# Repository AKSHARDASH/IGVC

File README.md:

# Team Anvrit - IGVC AutoNav Participation

Welcome to the repository for Team Anvrit's contribution to the IGVC AutoNav competition, hosted by Oakland University. This repository contains the schematic and board files for the custom PCB used in our vehicle.

## Overview

Our PCB design incorporates several unique features essential for tackling the problem statements of the IGVC AutoNav. The key functionalities of the PCB include:

- **Radio Kill Switch**: Utilizes a 433 MHz wireless receiver fixed on the PCB for remote vehicle shutdown.
- **Low Battery Kill Switch**: Implemented using a TL431 IC to ensure safe operation by shutting down the system when the battery voltage drops below a threshold.
- **Sensor Data Handling**: An Arduino Nano collects data from various sensors such as GPS, IMU, and wheel encoders, and transmits the data to the controlling computer using serial communication.

## PCB Features

### Radio Kill Switch

The radio receiver is active low. A simple yet efficient method to kill the vehicle wirelessly is devised using an AND gate IC. The two inputs of the AND gate are the required PWM signal and the radio data. When data is received, the data pin goes low, resulting in the output of the AND gate (connected to the motor driver) being 0, effectively stopping the vehicle.

### Low Battery Kill Switch

A TL431 IC is used to monitor the battery voltage. The reference terminal of the TL431 is kept above 2.5V using a simple voltage divider network. When the battery voltage falls below a certain threshold, the TL431 stops driving the PMOS connected to it, shutting down the entire system to prevent damage.

## System Architecture

1. **Sensor Data Collection**: An Arduino Nano gathers data from the GPS, IMU, and wheel encoders.
2. **Data Transmission**: The Arduino Nano sends the collected sensor data to the controlling computer via serial communication.
3. **ROS Integration**: The computer runs a ROS script that reads the data and publishes it to a ROS topic for further processing.
4. **Motor Control**: The computer calculates the desired RPM and sends this information back to the Arduino Nano. The Arduino then controls the motors by adjusting the PWM values accordingly.

## Repository Contents

- **Schematics**: The schematic files for the PCB design.
- **Board Files**: The board layout files for the PCB.

## Getting Started

To get started with using the PCB and running the vehicle, follow these steps:

1. **Clone the Repository**: Clone this repository to your local machine using `git clone`.
2. **Upload Arduino Code**: Upload the Arduino code to the Arduino Nano.
3. **Run ROS Script**: Set up and run the ROS script on the controlling computer to handle the sensor data and motor control.

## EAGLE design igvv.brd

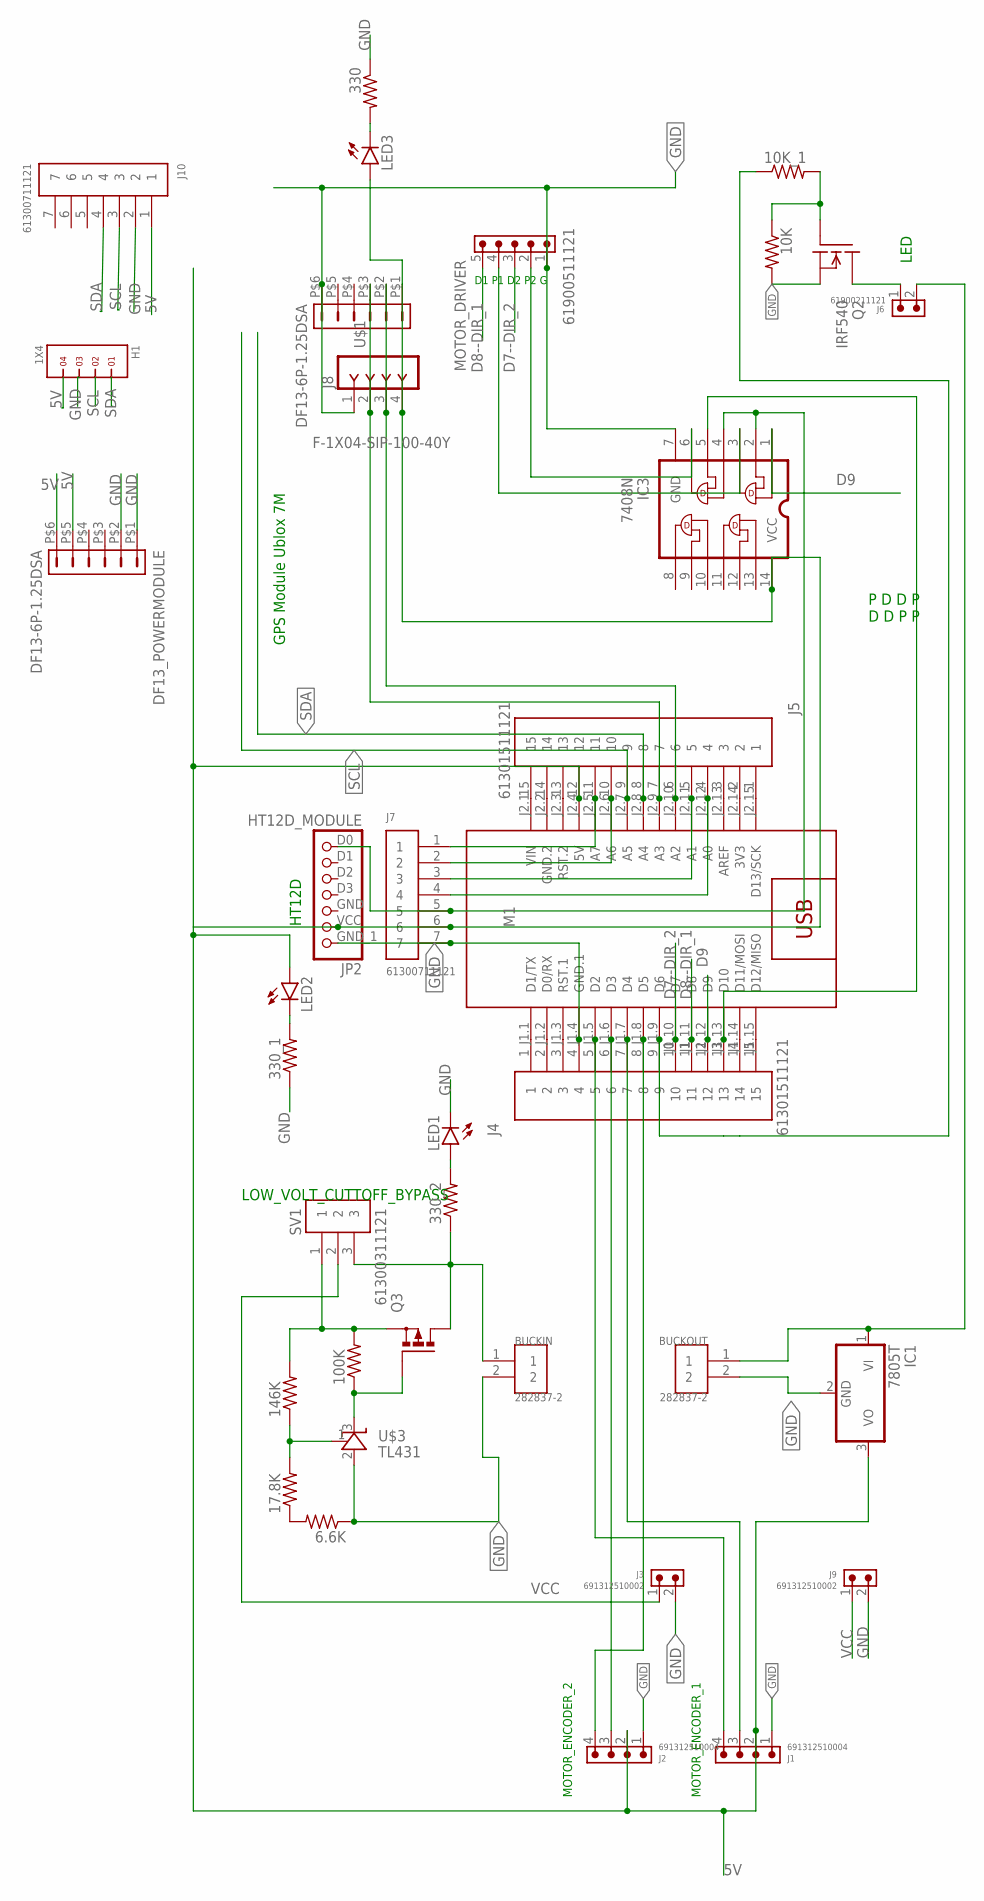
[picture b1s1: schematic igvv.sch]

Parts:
6.6K, 10K, 10K_1, 17.8K, 100K, 146K, 330, 330_1, 330_2: R-US_0207/10; 0207/10
BUCKIN: 282837-2; TE_282837-2
BUCKOUT: 282837-2; TE_282837-2
DF13_POWERMODULE: DF13-6P-1.25DSA
H1: 1X4
IC1: 7805T; TO220H
IC3: 7408N; DIL14
J1, J2: 691312510004
J3, J9: 691312510002
J4, J5: 61301511121
J6: 61900211121
J7, J10: 61300711121
J8: F-1X04-SIP-100-40Y; SIP-100-04-40Y
JP2: HT12D_MODULE
LED1, LED2, LED3: LED5MM
M1: ARDUINO-NANO-3.0ARDUINO-NANO-3.0; ARDUINO-NANO-3.0
MOTOR_DRIVER: 61900511121
Q2: IRF540; TO220
Q3: PMOSFET_PTO220BV; TO220BV
SV1: 61300311121
U$1: DF13-6P-1.25DSA
U$3: TL431; TO-92

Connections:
5V: DF13_POWERMODULE.P$5 (5), DF13_POWERMODULE.P$6 (6), H1.4, IC1.3 (VO), IC3.14 (VCC), J1.2, J2.2, J5.12, J7.6, J8.4, J10.1, JP2.VCC (2), LED2.A, LED3.A, M1.J2.4 (5V), U$1.P$1 (1)
A2: J5.6, J8.3, M1.J2.10 (A2), U$1.P$2 (2)
D4: J1.3, J4.7, M1.J1.7 (D4)
D7--DIR_2: J4.10, M1.J1.10 (D7), MOTOR_DRIVER.3
D8--DIR_1: J4.11, M1.J1.11 (D8), MOTOR_DRIVER.5
D9: IC3.1, J4.12, M1.J1.12 (D9)
GND: 6.6K.1, 10K.2, 330.1, 330_1.1, BUCKIN.2, BUCKOUT.2, DF13_POWERMODULE.P$1 (1), DF13_POWERMODULE.P$2 (2), H1.3, IC1.2 (GND), IC3.7 (GND), J1.1, J2.1, J3.2, J4.4, J7.7, J8.1, J9.2, J10.2, JP2.GND_1 (1), LED1.K (C), M1.J1.4 (GND.1), MOTOR_DRIVER.1, Q2.3 (S), U$1.P$6 (6), U$3.2 (A)
unnamed: 6.6K.2, 17.8K.1
unnamed: 17.8K.2, 146K.1, U$3.1 (REF)
unnamed: J1.4, J4.5, M1.J1.5 (D2)
unnamed: 100K.1, Q3.G, U$3.3 (C)
unnamed: 330_2.1, BUCKIN.1, Q3.D, SV1.3
unnamed: 100K.2, 146K.2, Q3.S, SV1.1
unnamed: BUCKOUT.1, IC1.1 (VI), J6.2
unnamed: J2.3, J4.6, M1.J1.6 (D3)
unnamed: J2.4, J4.8, M1.J1.8 (D5)
unnamed: 10K_1.1, J4.9, M1.J1.9 (D6)
unnamed: 330.2, LED3.K (C)
unnamed: J5.4, J7.4, M1.J2.12 (A0)
unnamed: J5.5, J7.3, M1.J2.11 (A1)
unnamed: J5.10, J7.2, M1.J2.6 (A6)
unnamed: J5.11, J7.1, M1.J2.5 (A7)
unnamed: 330_2.2, LED1.A
unnamed: 330_1.2, LED2.K (C)
unnamed: J4.1, M1.J1.1 (D1/TX)
unnamed: J5.7, J8.2, M1.J2.9 (A3), U$1.P$3 (3)
unnamed: IC3.2, IC3.4, J7.5, JP2.D0 (7)
unnamed: J4.2, M1.J1.2 (D0/RX)
unnamed: J4.3, M1.J1.3 (RST.1)
unnamed: J4.14, M1.J1.14 (D11/MOSI)
unnamed: J4.15, M1.J1.15 (D12/MISO)
unnamed: J5.1, M1.J2.15 (D13/SCK)
unnamed: J5.2, M1.J2.14 (3V3)
unnamed: J5.3, M1.J2.13 (AREF)
unnamed: J5.13, M1.J2.3 (RST.2)
unnamed: J5.14, M1.J2.2 (GND.2)
unnamed: J5.15, M1.J2.1 (VIN)
unnamed: 10K.1, 10K_1.2, Q2.1 (G)
unnamed: J6.1, Q2.2 (D)
unnamed: IC3.5, J4.13, M1.J1.13 (D10)
unnamed: IC3.3, MOTOR_DRIVER.4
unnamed: IC3.6, MOTOR_DRIVER.2
SCL: H1.2, J5.9, J10.3, M1.J2.7 (A5)
SDA: H1.1, J5.8, J10.4, M1.J2.8 (A4)
VCC: J3.1, J9.1, SV1.2

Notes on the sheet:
HT12D
MOTOR_ENCODER_1
LOW_VOLT_CUTTOFF_BYPASS
MOTOR_ENCODER_2
GPS Module Ublox 7M
LED
D1 P1 D2 P2 G
P D D P D D P P

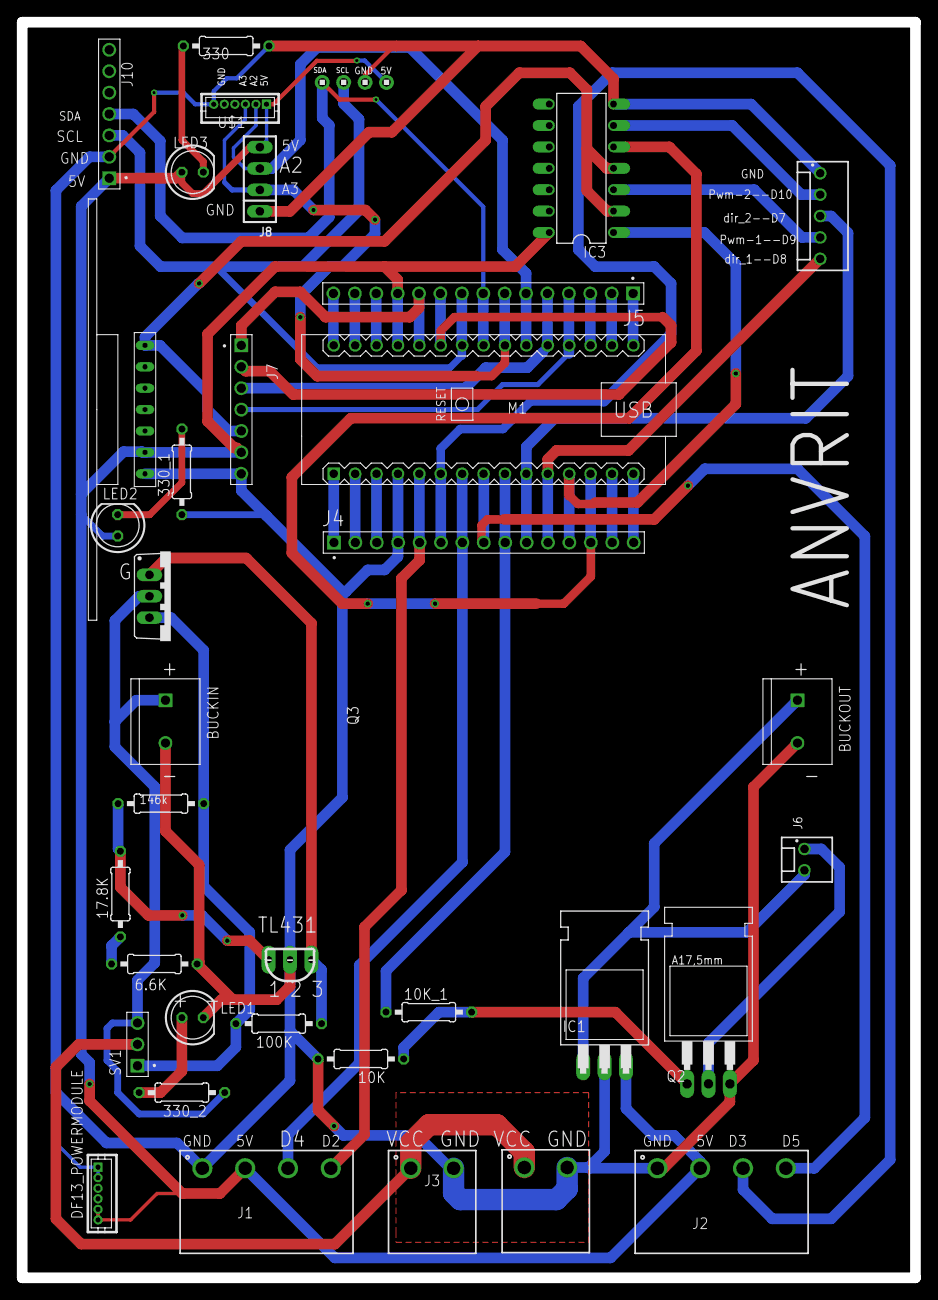
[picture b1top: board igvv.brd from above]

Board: 2 copper layers, 106.0 x 149.0 mm, 36 parts (0 on the bottom side), 45 nets.

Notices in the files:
parts and their libraries:
Wurth_Connectors_WR-TBL Pluggable Connec: Copyright: Würth Elektronik
con-headers-jp: Copyright (C) 2008, Bob Starr
